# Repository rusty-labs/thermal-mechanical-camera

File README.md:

Building a cheap and simple thermal, mechanical camera.

Specs:
 Taking 400x200 image takes roughly 30 min. 

Hardware requirements:
 1. Metallized, parabolic mirror - "Survival Solar Lighter".
 2. 3D printed mounts for motors and mirror.
 3. Two stepper motors - 28byj-48, these motors will be used as bipolar motors.
 4. Two motor controllers based on L293D.
 5. Thermopile sensor:

   a) TS118, needs additional circuitry for amplifying the signal.
   
   b) MLX90614ESF, has circuitry inside so you don't need to create one (Recommended choice!).
   
 6. Amplifying circuitry, needed only if you're going to use TS118.
 7. Arduino
 8. MicroSD card module for arduino

Arduino code:

   a) For MLX90614ESF, this sensor returns temperature by I2C protocol.
   
   b) For TS118, this sensor returns analogue signal, which will be converted to temperature afterwards.

Overall cost - 25$.

Folders descriptions:

1. arduino\scanner - contains arduino code for running the scanning process.
2. circuits - contains circuits for stepper controller and signal amplification.
3. 3d-models - containts 3d models of mounts.
4. sample-images - contains thermal images.
5. scanner-photos - contains photos of a scanner.

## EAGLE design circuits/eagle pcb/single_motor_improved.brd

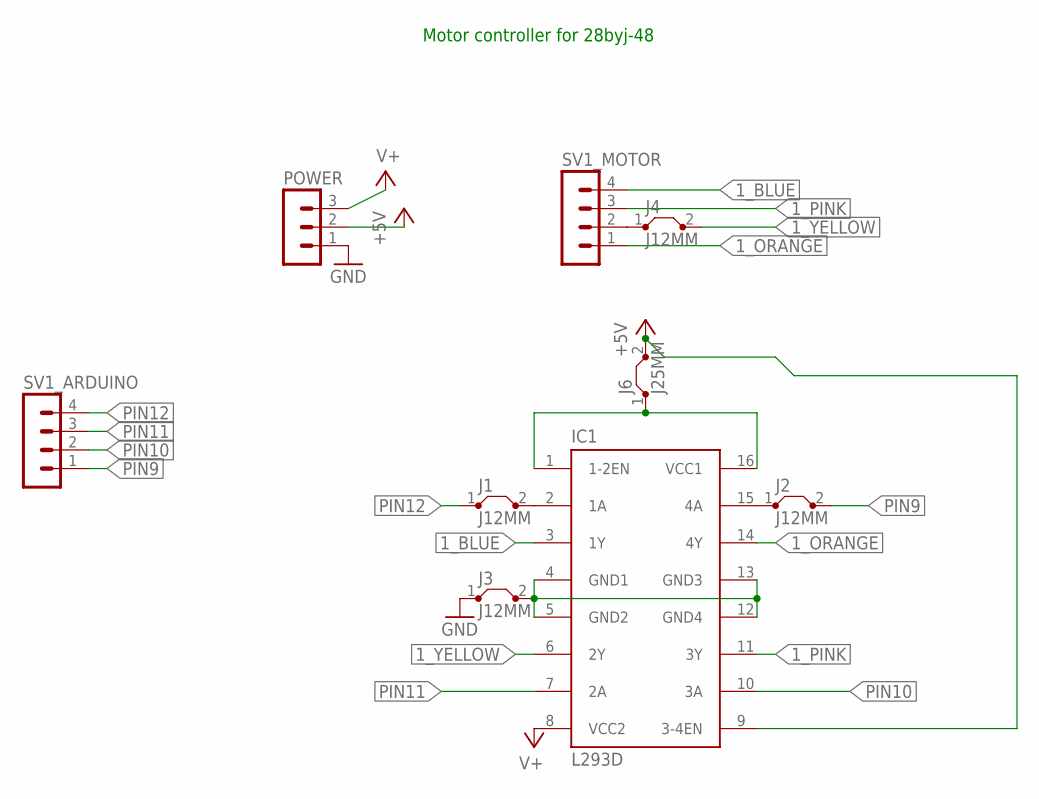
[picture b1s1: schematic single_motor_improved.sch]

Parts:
IC1: L293D; DIL16
J1, J2, J3, J4: J12MM; 12
J6: J25MM; 25
POWER: MA03-1
SV1_ARDUINO, SV1_MOTOR: MA04-1

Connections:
1_BLUE: IC1.3 (1Y), SV1_MOTOR.4
1_ORANGE: IC1.14 (4Y), SV1_MOTOR.1
1_PINK: IC1.11 (3Y), SV1_MOTOR.3
1_YELLOW: IC1.6 (2Y), J4.2
+5V: IC1.9 (3-4EN), J6.2, POWER.2
GND: J3.1, POWER.1
unnamed: IC1.2 (1A), J1.2
unnamed: IC1.15 (4A), J2.1
unnamed: IC1.1 (1-2EN), IC1.16 (VCC1), J6.1
unnamed: J4.1, SV1_MOTOR.2
unnamed: IC1.4 (GND1), IC1.5 (GND2), IC1.12 (GND4), IC1.13 (GND3), J3.2
PIN9: J2.2, SV1_ARDUINO.1
PIN10: IC1.10 (3A), SV1_ARDUINO.2
PIN11: IC1.7 (2A), SV1_ARDUINO.3
PIN12: J1.1, SV1_ARDUINO.4
V+: IC1.8 (VCC2), POWER.3

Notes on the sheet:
Motor controller for 28byj-48

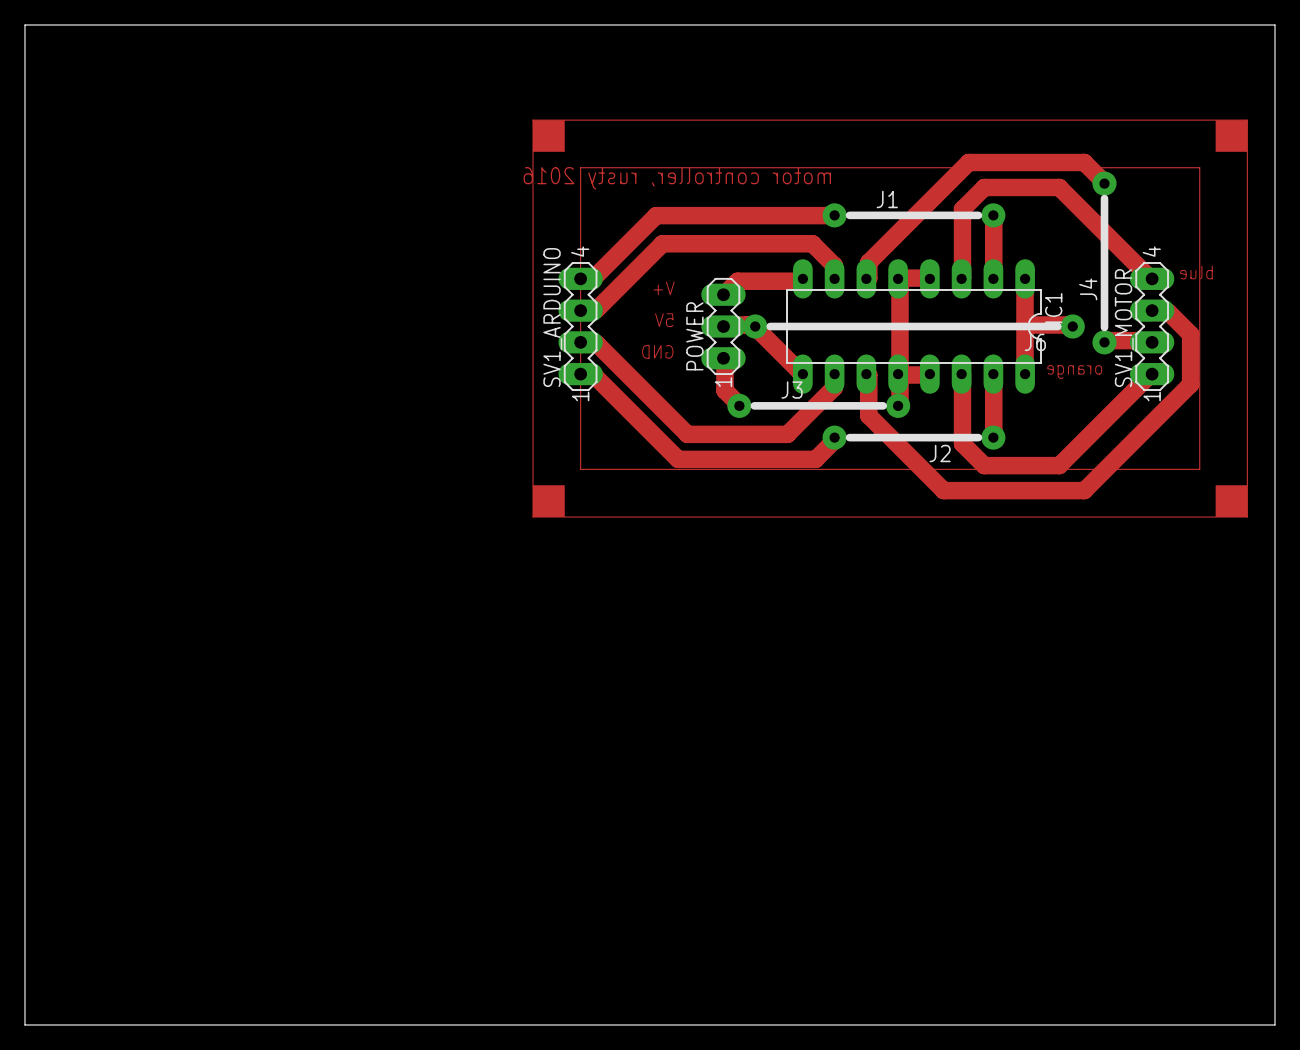
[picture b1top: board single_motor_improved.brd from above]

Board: 2 copper layers, 100.0 x 80.0 mm, 9 parts (0 on the bottom side), 16 nets.

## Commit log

2016-04-04 copied code from svn
2016-04-04 added circuit for TS118
2016-04-04 added sample image
2016-04-20 added license
2016-04-20 added photos
